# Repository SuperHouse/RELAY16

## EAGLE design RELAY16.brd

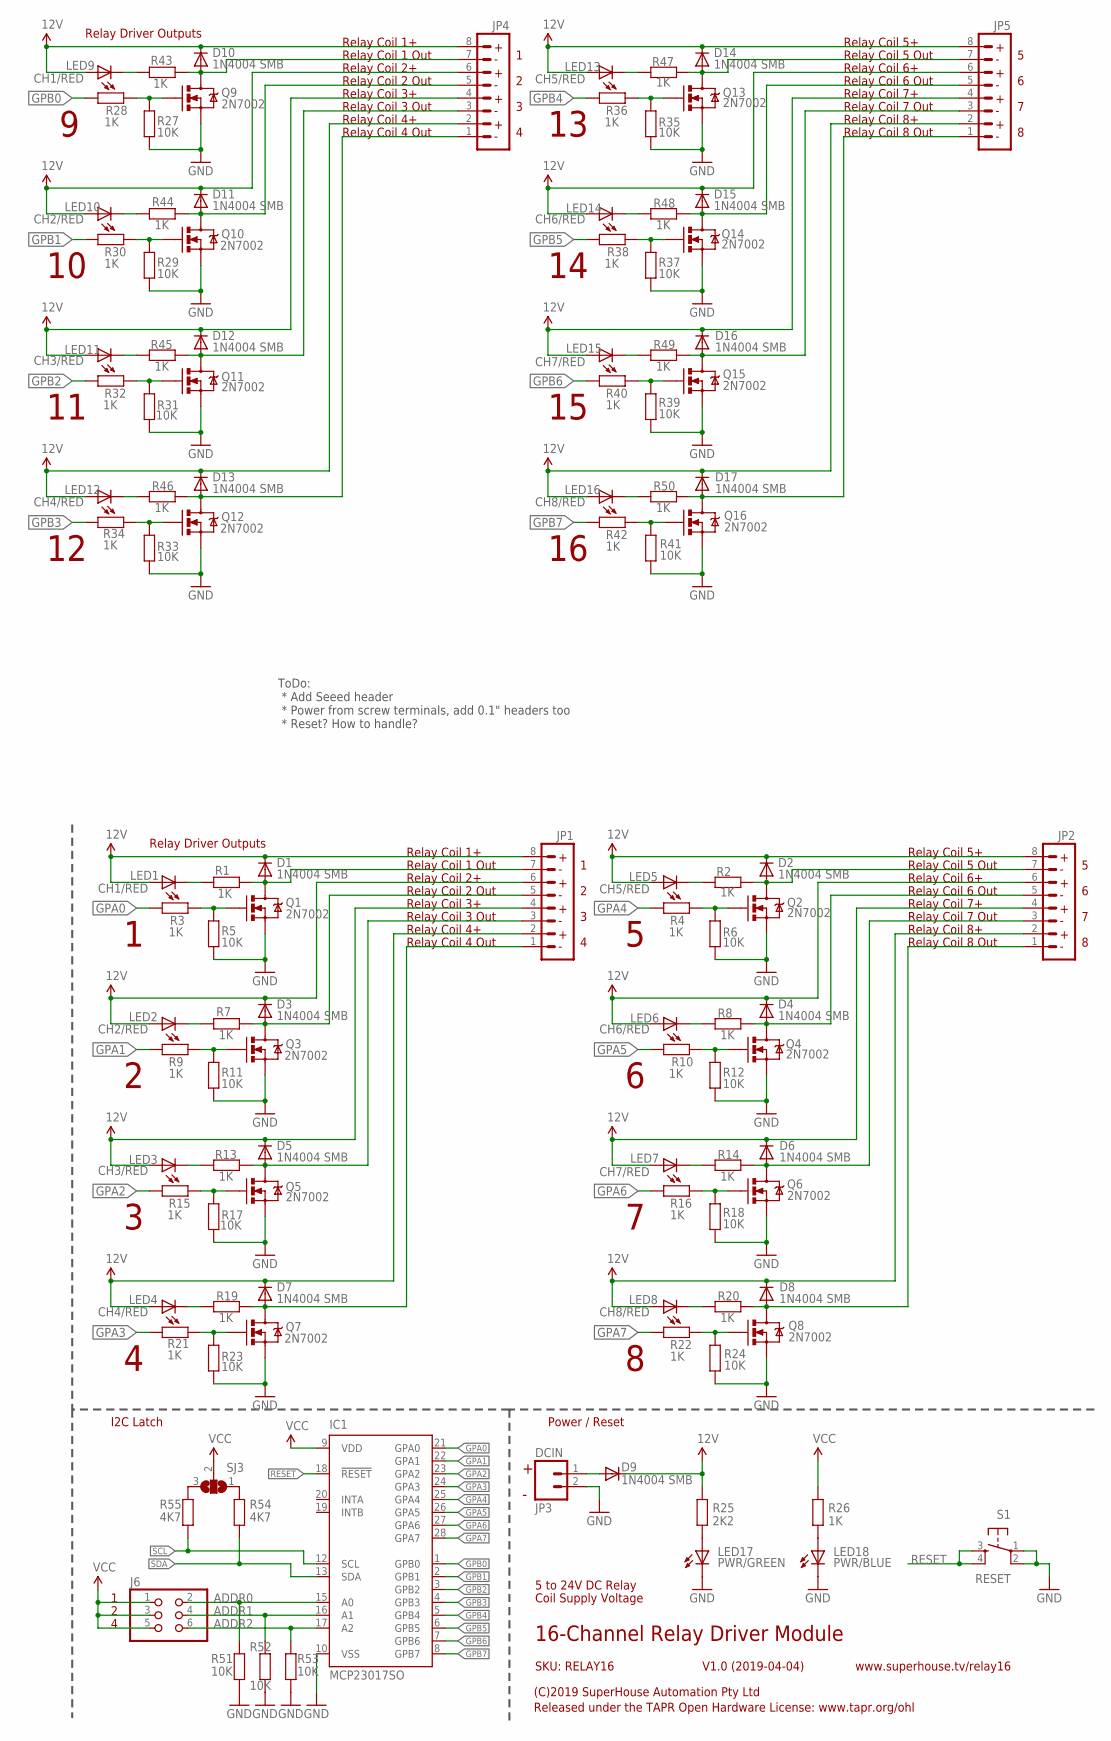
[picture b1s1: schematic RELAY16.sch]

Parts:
D1, D2, D3, D4, D5, D6, D7, D8, D9, D10, D11, D12, D13, D14, D15, D16, D17: 1N4004 SMB; SMB-DIODE
IC1: MCP23017SO; SO28W
J6: PINHD-2X3; 2X03
JP1, JP2, JP4, JP5: M08; TERMINALBLOCK_3.5MM_8
JP3: DCIN; SCREWTERMINAL-3.5MM-2
LED1, LED9: CH1/RED; LED-0603
LED2, LED10: CH2/RED; LED-0603
LED3, LED11: CH3/RED; LED-0603
LED4, LED12: CH4/RED; LED-0603
LED5, LED13: CH5/RED; LED-0603
LED6, LED14: CH6/RED; LED-0603
LED7, LED15: CH7/RED; LED-0603
LED8, LED16: CH8/RED; LED-0603
LED17: PWR/GREEN; LED-0603
LED18: PWR/BLUE; LED-0603
Q1, Q2, Q3, Q4, Q5, Q6, Q7, Q8, Q9, Q10, Q11, Q12, Q13, Q14, Q15, Q16: 2N7002; SOT23-3
R1, R2, R3, R4, R7, R8, R9, R10, R13, R14, R15, R16, R19, R20, R21, R22, R26, R28, R30, R32, R34, R36, R38, R40, R42, R43, R44, R45, R46, R47, R48, R49, R50: 1K; 0603
R5, R6, R11, R12, R17, R18, R23, R24, R27, R29, R31, R33, R35, R37, R39, R41, R51, R52, R53: 10K; 0603
R25: 2K2; 0603
R54, R55: 4K7; 0603
S1: RESET; TACTILE_SWITCH_SMD
SJ3: SJ2W; SJ_2

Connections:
12V: D1.C, D2.C, D3.C, D4.C, D5.C, D6.C, D7.C, D8.C, D9.C, D10.C, D11.C, D12.C, D13.C, D14.C, D15.C, D16.C, D17.C, JP1.2, JP1.4, JP1.6, JP1.8, JP2.2, JP2.4, JP2.6, JP2.8, JP4.2, JP4.4, JP4.6, JP4.8, JP5.2, JP5.4, JP5.6, JP5.8, LED1.A, LED2.A, LED3.A, LED4.A, LED5.A, LED6.A, LED7.A, LED8.A, LED9.A, LED10.A, LED11.A, LED12.A, LED13.A, LED14.A, LED15.A, LED16.A, R25.2
ADDR0: IC1.15 (A0), J6.2, R51.2
ADDR1: IC1.16 (A1), J6.4, R52.2
ADDR2: IC1.17 (A2), J6.6, R53.2
GND: IC1.10 (VSS), JP3.2, LED17.C, LED18.C, Q1.2 (S), Q2.2 (S), Q3.2 (S), Q4.2 (S), Q5.2 (S), Q6.2 (S), Q7.2 (S), Q8.2 (S), Q9.2 (S), Q10.2 (S), Q11.2 (S), Q12.2 (S), Q13.2 (S), Q14.2 (S), Q15.2 (S), Q16.2 (S), R5.1, R6.1, R11.1, R12.1, R17.1, R18.1, R23.1, R24.1, R27.1, R29.1, R31.1, R33.1, R35.1, R37.1, R39.1, R41.1, R51.1, R52.1, R53.1, S1.1, S1.2
GPA0: IC1.21 (GPA0), R3.2
GPA1: IC1.22 (GPA1), R9.2
GPA2: IC1.23 (GPA2), R15.2
GPA3: IC1.24 (GPA3), R21.2
GPA4: IC1.25 (GPA4), R4.2
GPA5: IC1.26 (GPA5), R10.2
GPA6: IC1.27 (GPA6), R16.2
GPA7: IC1.28 (GPA7), R22.2
GPB0: IC1.1 (GPB0), R28.2
GPB1: IC1.2 (GPB1), R30.2
GPB2: IC1.3 (GPB2), R32.2
GPB3: IC1.4 (GPB3), R34.2
GPB4: IC1.5 (GPB4), R36.2
GPB5: IC1.6 (GPB5), R38.2
GPB6: IC1.7 (GPB6), R40.2
GPB7: IC1.8 (GPB7), R42.2
IOREF: IC1.9 (VDD), J6.1, J6.3, J6.5, R26.2, SJ3.2
unnamed: Q1.1 (G), R3.1, R5.2
unnamed: R55.2, SJ3.3
unnamed: D3.A, JP1.5, Q3.3 (D), R7.2
unnamed: LED17.A, R25.1
unnamed: D1.A, JP1.7, Q1.3 (D), R1.2
unnamed: R54.2, SJ3.1
unnamed: Q3.1 (G), R9.1, R11.2
unnamed: D5.A, JP1.3, Q5.3 (D), R13.2
unnamed: Q5.1 (G), R15.1, R17.2
unnamed: D7.A, JP1.1, Q7.3 (D), R19.2
unnamed: Q7.1 (G), R21.1, R23.2
unnamed: D2.A, JP2.7, Q2.3 (D), R2.2
unnamed: Q2.1 (G), R4.1, R6.2
unnamed: D4.A, JP2.5, Q4.3 (D), R8.2
unnamed: Q4.1 (G), R10.1, R12.2
unnamed: D6.A, JP2.3, Q6.3 (D), R14.2
unnamed: Q6.1 (G), R16.1, R18.2
unnamed: D8.A, JP2.1, Q8.3 (D), R20.2
unnamed: Q8.1 (G), R22.1, R24.2
unnamed: LED2.C, R7.1
unnamed: LED4.C, R19.1
unnamed: LED3.C, R13.1
unnamed: LED1.C, R1.1
unnamed: LED5.C, R2.1
unnamed: LED6.C, R8.1
unnamed: LED7.C, R14.1
unnamed: LED8.C, R20.1
unnamed: D9.A, JP3.1
unnamed: D10.A, JP4.7, Q9.3 (D), R43.2
unnamed: Q9.1 (G), R27.2, R28.1
unnamed: D11.A, JP4.5, Q10.3 (D), R44.2
unnamed: Q10.1 (G), R29.2, R30.1
unnamed: D12.A, JP4.3, Q11.3 (D), R45.2
unnamed: Q11.1 (G), R31.2, R32.1
unnamed: LED18.A, R26.1
unnamed: D13.A, JP4.1, Q12.3 (D), R46.2
unnamed: Q12.1 (G), R33.2, R34.1
unnamed: D14.A, JP5.7, Q13.3 (D), R47.2
unnamed: Q13.1 (G), R35.2, R36.1
unnamed: D15.A, JP5.5, Q14.3 (D), R48.2
unnamed: Q14.1 (G), R37.2, R38.1
unnamed: D16.A, JP5.3, Q15.3 (D), R49.2
unnamed: Q15.1 (G), R39.2, R40.1
unnamed: D17.A, JP5.1, Q16.3 (D), R50.2
unnamed: Q16.1 (G), R41.2, R42.1
unnamed: LED9.C, R43.1
unnamed: LED10.C, R44.1
unnamed: LED11.C, R45.1
unnamed: LED12.C, R46.1
unnamed: LED13.C, R47.1
unnamed: LED14.C, R48.1
unnamed: LED15.C, R49.1
unnamed: LED16.C, R50.1
RESET: IC1.18 (!RESET), S1.3, S1.4
SCL: IC1.12 (SCL), R55.1
SDA: IC1.13 (SDA), R54.1

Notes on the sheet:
16-Channel Relay Driver Module
V1.0 (2019-04-04)
SKU: RELAY16
Power / Reset
(C)2019 SuperHouse Automation Pty Ltd
Released under the TAPR Open Hardware License: www.tapr.org/ohl
www.superhouse.tv/relay16
Relay Coil 1 Out
Relay Coil 1+
Relay Coil 2+
Relay Coil 3+
Relay Coil 4+
Relay Coil 4 Out
Relay Coil 3 Out
Relay Coil 2 Out
Relay Coil 8 Out
Relay Coil 8+
Relay Coil 5+
Relay Coil 5 Out
Relay Coil 6+
Relay Coil 6 Out
Relay Coil 7+
Relay Coil 7 Out
5 to 24V DC Relay
Coil Supply Voltage
Relay Driver Outputs
I2C Latch
ToDo: * Add Seeed header * Power from screw terminals, add 0.1" headers too * Reset? How to handle?

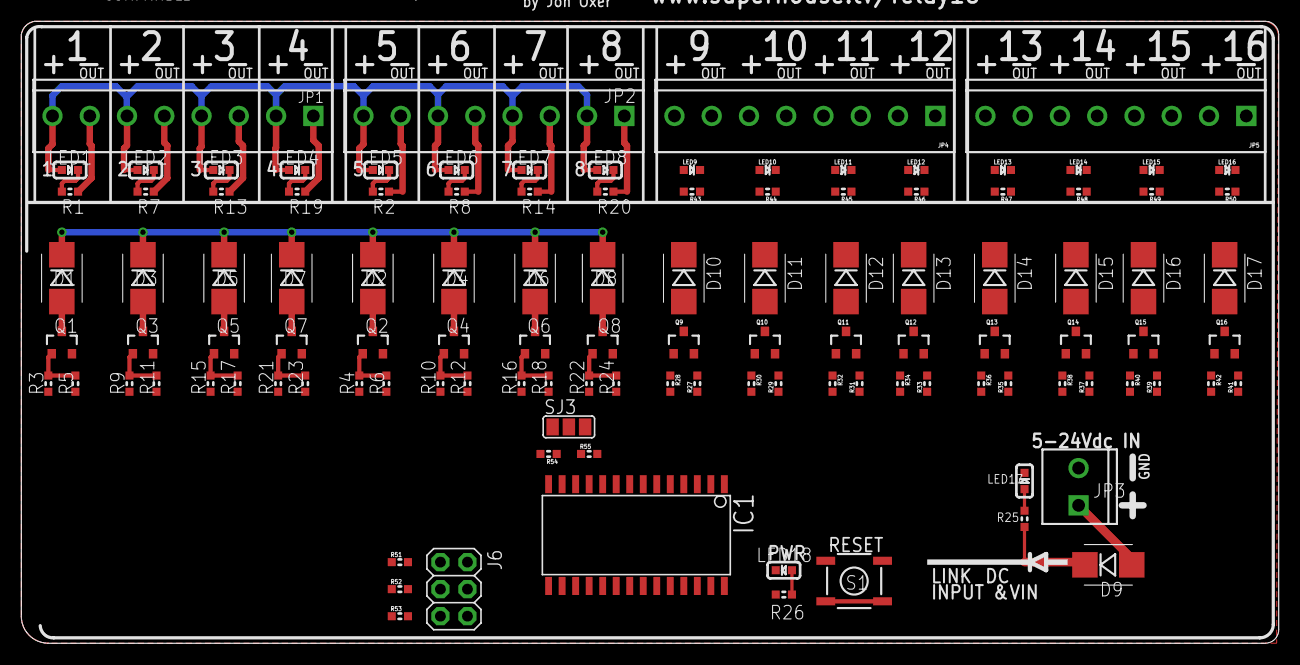
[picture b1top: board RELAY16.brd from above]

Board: 2 copper layers, 118.1 x 58.4 mm, 116 parts (1 on the bottom side), 78 nets.

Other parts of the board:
U$6: OSHW_10X200_NOTEXT

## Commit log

2019-04-04 Import of files
2019-04-24 Rough draft

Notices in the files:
RELAY16.brd:
(c) 2012-14 Freetronics Pty Ltd
Hardware License: tapr.org/OHL
